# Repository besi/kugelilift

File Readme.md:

Kugelilift
==========

Check out the sources:

    git submodule update --init --recursive

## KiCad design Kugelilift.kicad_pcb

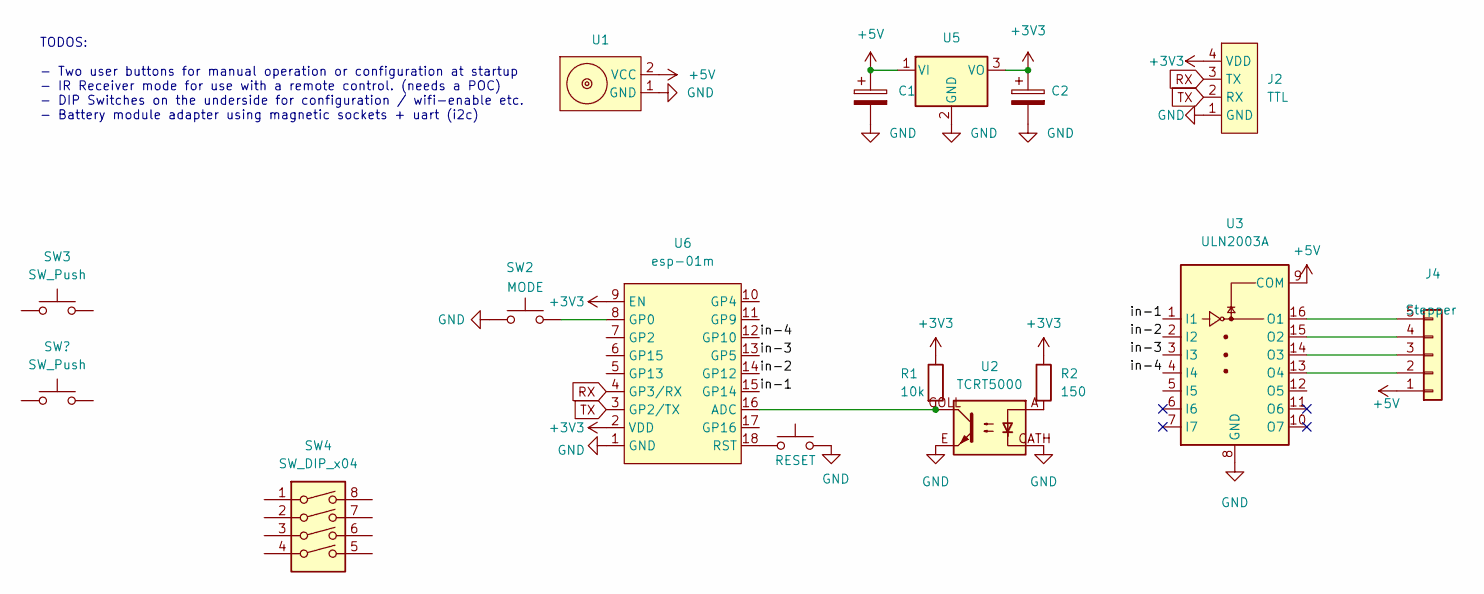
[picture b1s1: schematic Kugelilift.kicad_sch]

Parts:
C1, C2: C_Polarized; CP_Radial_D6.3mm_P2.50mm
J2: TTL; PinHeader_1x04_P2.54mm_Vertical
J4: Stepper; JST_EH_B5B-EH-A_1x05_P2.50mm_Vertical
R1: 10k; R_Axial_DIN0207_L6.3mm_D2.5mm_P10.16mm_Horizontal
R2: 150; R_Axial_DIN0207_L6.3mm_D2.5mm_P7.62mm_Horizontal
SW1: RESET; PinHeader_1x03_P2.54mm_Vertical
SW2: MODE; PinHeader_1x03_P2.54mm_Vertical
SW3: SW_Push; SW_Push_1P1T_NO_CK_KMR2
SW4: SW_DIP_x04; SW_DIP_SPSTx04_Slide_6.7x11.72mm_W7.62mm_P2.54mm_LowProfile
U1: magnetic-charger
U2: TCRT5000; tcrt5000
U3: ULN2003A; SOP-16_4.55x10.3mm_P1.27mm
U5: UA78M33_TO252; TO-252-2
U6: esp-01m

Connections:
+3V3: C2.1, J2.4 (VDD), R1.1, R2.1, U5.3 (VO), U6.2 (VDD), U6.9 (EN)
+5V: C1.1, J4.1, U1.2 (VCC), U3.9 (COM), U5.1 (VI)
/in-1: U3.1 (I1), U6.15 (GP14)
/in-2: U3.2 (I2), U6.14 (GP12)
/in-3: U3.3 (I3), U6.13 (GP5)
/in-4: U3.4 (I4), U6.12 (GP10)
GND: C1.2, C2.2, J2.1 (GND), SW1.2, SW2.2, U1.1 (GND), U2.CATH, U2.E, U3.8 (GND), U5.2 (GND), U6.1 (GND)
unnamed: J4.2, U3.13 (O4)
unnamed: J4.3, U3.14 (O3)
unnamed: J4.4, U3.15 (O2)
unnamed: J4.5, U3.16 (O1)
unnamed: R1.2, U2.COLL, U6.16 (ADC)
unnamed: R2.2, U2.A
unnamed: SW1.1, U6.18 (RST)
unnamed: SW2.1, U6.8 (GP0)
RX: J2.3 (TX), U6.4 (GP3/RX)
TX: J2.2 (RX), U6.3 (GP2/TX)

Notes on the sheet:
TODOS: - Two user buttons for manual operation or configuration at startup - IR Receiver mode for use with a remote control. (needs a POC) - DIP Switches on the underside for configuration / wifi-enable etc. - Battery module adapter using magnetic sockets + uart (i2c)

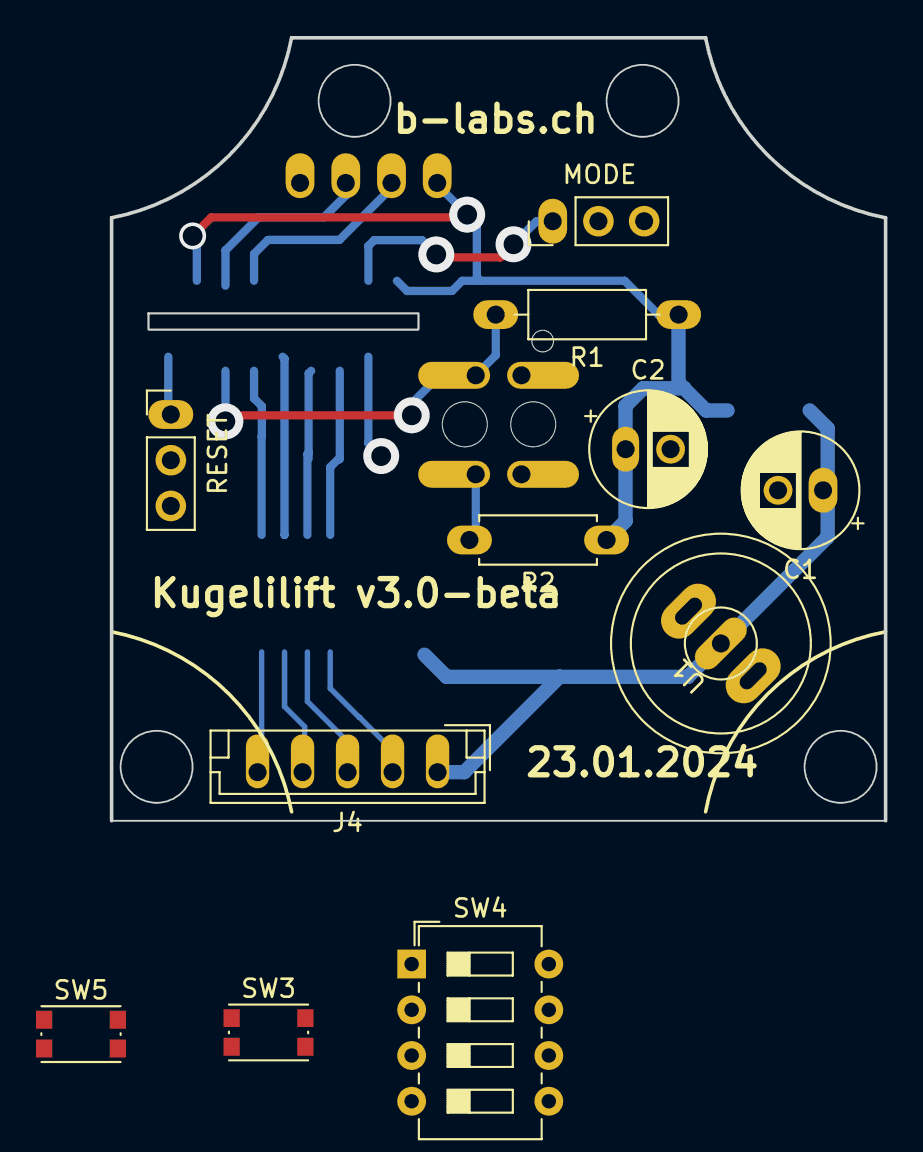
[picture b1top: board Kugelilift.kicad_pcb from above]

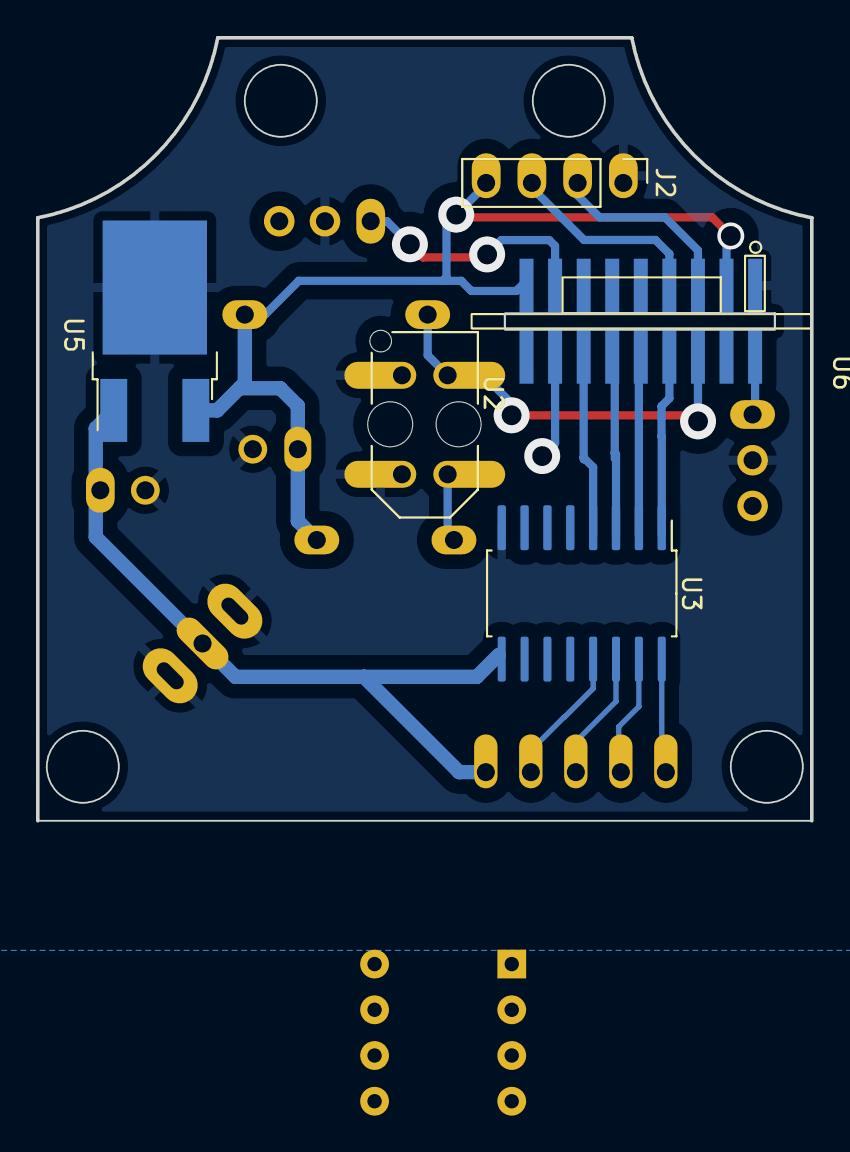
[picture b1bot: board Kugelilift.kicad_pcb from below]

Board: 2 copper layers, 43.0 x 43.5 mm, 16 parts (5 on the bottom side), 17 nets.

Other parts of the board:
SW5: SW_Push; SW_Push_1P1T_NO_CK_KMR2

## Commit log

2023-12-14 Initial commit of Kugelilift PCB
2023-12-14 Add software
2023-12-14 Working progres with SMT ESP12 module
2023-12-14 ESP-01F based PCB
2023-12-15 PCB Version 2.2
    - ESP-12F
    - Linear regulator + Capacitors
    - ULN2003 in small SOP-16 package
    - TTL instead of USB
    - TCRT5000
2023-12-15 Prepare for milling
2023-12-15 Small adjustments for milling
2023-12-16 Add labels for header-buttons
2023-12-16 PCB based on ESP01m
2023-12-16 Export 3D File
2023-12-16 Small rearrangements
2023-12-18 Final adjustments
2023-12-22 Add correction factor for the stepper motor
2023-12-22 Make four rotations when a ball is detected
2023-12-22 Fine tune the lift software
2023-12-22 Add wifi capabilities
2024-01-21 Add 3d models
2024-01-23 Prepare for next iteration
2024-01-23 Cleanup stls
2024-02-01 Disable the WIFI since it’s not used mostly
    Opens #1
2024-02-01 Nod hello when switched on and adjust for tripple 180degree sprial
2024-02-07 3d print top and bottom
2025-01-08 Add 3d model
2025-02-22 adjust threshold
2025-03-07 Add photo of the acutual elevator
2025-03-12 Add Fusoin360 model and rename the pcb step file
    See #2
